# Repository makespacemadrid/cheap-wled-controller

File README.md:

Este proyecto nace de una práctica con Kicad en uno de los talleres de Makespace (slides de nuestro compañero Pablo Garrido [aquí](https://docs.google.com/presentation/d/1glYFRo9XCKRI-qDjp1DA8M3mJohLk-lrxx0JoBPsboM/edit?usp=drive_link)),
donde se diseñó el esquemático y el enrutado de la pcb para posterior fabricación de la misma en JLCPCB.

Continuando con el proceso lógico de aprendizaje, 
ahora este proyecto pretende servir como una primera aproximación en la práctica de soldadura SMD (componentes de montaje superficiales), 
así como fabricación de stencil usando una CNC (maquina de control numérico).

Junto al proyecto Kicad también se encuentran los stl de la carcasa para imprimirla en 3d.

El repositorio con el proyecto Kicad: https://github.com/makespacemadrid/cheap-wled-controller718714

Esta pcb tiene la particularidad de usar para su alimentación un usb c con PD (Power delivery), lo que permite negociar diferentes votlajes y de este modo usar tiras led que trabajen a 5v, 9v, 12v, etc.

## BOM 
### PCB
- [CH224K USB PD Protocol Sink Chip IC 10Pcs/lot](https://www.aliexpress.com/item/1005005284290184.html?spm=a2g0o.order_list.order_list_main.5.21ef194dDFnpwX)
- [AMS1117 3.3](https://www.aliexpress.com/item/1005005350284100.html?spm=a2g0o.order_list.order_list_main.544.21ef194dDFnpwX)
- ESP32-S3-WROOM-1-N4R
- [TPS54202DDC](https://lcsc.com/product-detail/DC-DC-Converters_TI-TPS54202DDCR_C191884.html?s_z=n_C191884)
- [MX5014S](https://lcsc.com/product-detail/Gate-Drivers_Wuxi-Maxinmicro-MX5014S_C5359091.html?s_z=n_C5359091)
- [ESDA25W](https://lcsc.com/product-detail/ESD-and-Surge-Protection-TVS-ESD_TECH-PUBLIC-ESDA25W_C3021136.html?s_z=n_C3021136)
- [receptor IR](https://lcsc.com/product-detail/Infrared-Receivers_VISHAY_TSOP38238_TSOP38238_C141632.html)
- diodo led footprint 0805
- [conector usb C](https://lcsc.com/product-detail/USB-Connectors_Korean-Hroparts-Elec-TYPE-C-31-M-12_C165948.html?s_z=n_C165948)
- [pin-header](https://lcsc.com/product-detail/Pin-Headers_Megastar-ZX-PZ2-0-2-5PZZ_C7501288.html?s_z=n_C7501288)
- [mosfet canal N](https://lcsc.com/product-detail/MOSFETs_YANGJIE-YJG100N04A_C919580.html?s_z=n_C919580)

### Stencil
- [fresa 3.175mmx15Dx0.1, CN](https://www.aliexpress.com/item/4000966103866.html?spm=a2g0o.order_list.order_list_main.509.21ef194dDFnpwX)
- una lata de refresco
- cinta de carrocero
- cinta de doble cara sin espuma. La que usamos nosotros es esta, comprada en papelerías Folder:
[comprada en papelerías Folder](/images/cinta_doble_cara.png)

### Carcasa
- 4 tornillos M3x6
- 4 insertos metálicos [Length 4mm, M3 (OD 5mm)](https://es.aliexpress.com/item/1005004870993068.html?spm=a2g0o.order_list.order_list_main.17.506f194dqZ3Ccw&gatewayAdapt=glo2esp)

## Tiras led
Las tiras led compatibles con el firmware son: https://kno.wled.ge/basics/compatible-led-strips/
- La tira led que usamos en el taller es esta: [WS2813 DC5V, White PCB, 2m 60 IP65](https://es.aliexpress.com/item/1005004289391906.html?spm=a2g0o.order_list.order_list_main.10.5d6c194dSriMHZ&gatewayAdapt=glo2esp)
- Para la alimentación sirve cualquier cargador de móvil con carga rápida, IKEA tiene [estos](https://www.ikea.com/es/es/p/sjoss-cargador-usb-1-puerto-30-w-carga-rapida-50549412/) a muy buen precio
- [conectores hembra y macho JST SM de 4 pines](https://es.aliexpress.com/item/1005004615616698.html)

## Fabricación de stencil
Usaremos el software Flatcam, en el que cargamos la capa "paste top" del gerber que generamos en Kicad para enviar a fabricar la PCB.
Esta capa contiene la geometría de los pads de todos los componentes. 

El proceso lo vamos a llevar a cabo con una fresa de 30 grados y 0.1 de diámetro. Asumiendo que la lata de refresco tiene un grosor de 0.2mm.
Las capturas de los pasos a seguir son las siguientes:

El gcode generado finalmente lo hemos subido [aquí](/includes/paste_top.gcode).

## Flasheo y configuración de firmware WLED

### Flasheo

En nuestro caso estamos usando un esp32 s3 con 4MB, por lo que vamos a flashear desde la web: https://wled-install.github.io/

### Configuración
En LED preferences:

La configuración de la tira:

La configuración del mosfet para apagar la tira:

El botón en placa permite encender y apagar la tira manualmente:

Para configurar el mando usaremos [este](/includes/18-key-ir.json) fichero json.

## Software necesario
- [Kicad](https://www.kicad.org/): Diseño pcb y generación de gerbers.
- [Flatcam](http://flatcam.org/): **Solo windows (adjuntamos el gcode ya generado)** Creación de gcode a partir del gerber para la fabricación del stencil
- [gSender](https://sienci.com/gsender/?srsltid=AfmBOopYPgWM8177GG6Q0knLP97hrF1G2skJw3ewIg3omObme7XnkDx5): Comunicación con la CNC para enviar el gcode
- [OrcaSlicer](https://orca-slicer.com/): Cualquier slicer para impresora 3d para fabricar la carcasa.

## Esquema de la placa

En este apartado se describen los componentes principales del circuito para gestionar la alimentación y regulación del voltaje de la tira LED.

---

### Información sobre el power delivery

📄 [UPD301A USB Power Delivery Operation](/datasheet/AN3265MicroChip.pdf)

📄 [A Primer on USB Type-C® and USB Power Delivery Applications and Requirements](/datasheet/PowerDeliveryTexas.pdf)

### 🔌 Conector USB-C

El conector USB-C que se utiliza en la placa tiene doce patillas con una separación muy pequeña entre cada una de ellas; además, en los dos extremos se encuentran los pines de alimentación (GND y VBUS), por lo que una mala soldadura podría generar un cortocircuito. 

> **Es importante que antes de conectar la placa se mida la resistencia entre los pines de alimentación para comprobar que no haya cortocircuito 🔥.**

---

### CH224K

El CH224K es el componente encargado de gestionar el protocolo *power delibery* (PD).

📄 [Descargar datasheet](https://github.com/makespacemadrid/cheap-wled-controller/blob/main/datasheet/ch224k.pdf)

- **Encapsulado:** ESSOP-10
- **Distribución de pines:**

| Pin No.     | Pin name | Pin type          | Pin description                                                                 |
|-------------|----------|-------------------|----------------------------------------------------------------------------------|
| 0           | GND      | Power             | Ground. Heat dissipation EPAD.                                                  |
| 1           | VDD      | Power             | Operating power input. Requires external 1uF decoupling capacitor. Connected in series with a resistor to VBUS. |
| 4, 5        | DP, DM   | Input/Output      | USB data line                                                                   |
| 6, 7        | CC1, CC2 | Input/Output      | Type-C CC data line                                                             |
| 2, 3, 9     | CFG1, CFG2, CFG3 | Analog input     | Power configuration input                                                       |
| 8           | VBUS     | Analog input      | Voltage detection input. Connected in series with a resistor to external VBUS.  |
| 10          | PG       | Open-drain output | Indicates Power Good by default. Active low. Can be customized.                |

- **Configuración de voltaje de salida:**

  Los pines encargados de  configurar la salida del voltaje son el 2, el 3 y el 9. En este caso solo se utiliza el pin 9, por lo que en función de la resistencia que se conecte a este pin, el voltaje de salida variará entre 5 y 20 voltios.

   >Por ejemplo, si se conecta una resistencia de 10 kΩ del pin 9 a tierra, el voltaje de salida (VBUS_CONN) será de 5 V.

  | Resistance on CFG to VDD | Request-voltage |
  |--------------------------|-----------------|
  | 10KΩ                     | 5V              |
  | 20KΩ                     | 9V              |
  | 47KΩ                     | 12V             |
  | 100KΩ                    | 15V             |
  | 200KΩ                    | 20V             |

---
### TPS54202

El voltaje que sale del CH224K entra en el *buck converter* TPS54202, que será el encargado de generar los 5 voltios estables del circuito.

📄 [Descargar datasheet](/datasheet/tps54202.pdf)

- **Encapsulado:** SOT-23
  
- **Distribución de pines:**

- **Configuración del circuito:**
  
  En el esquema del circuito se puede observar la configuración del componente, compuesta por resistencias, condensadores y la bobina L2, que mediante su carga (en forma de campo magnético) y descarga genera la corriente necesaria para alimentar los condensadores, que estabilizarán los 5 voltios de salida (+5V).

---
### AMS1117 3-3V

Una vez que se ha generado el voltaje +5V, el regulador de voltaje lineal (LDO) AMS1117 comienza a trabajar para entregar los 3,3V. Hay que tener en cuenta que la corriente máxima que puede entregar este regulador es de 1A. 

📄 [Descargar datasheet](/datasheet/ams1117.pdf)

- **Distribución de pines:**

  > PIN 1: GND
  >
  > PIN 2: VOUT
  >
  > PIN 3: VDD

- **Configuración del circuito:**

---
### ESP32-S3-WROOM-1-N4R2

📄 [Descargar datasheet](/datasheet/esp32-s3.pdf)

- **Distribución de pines:**

- **Configuración del circuito:**

---
### MX5014S

 La tira LED se alimenta a través del voltaje que se genera en el MOSFET Q3, que está controlado por el MX5014S, y que a su vez responde del IO47 del ESP32.

📄 [Descargar datasheet](/datasheet/mx5014s.pdf)

- **Distribución de pines:**

- **Configuración del circuito:**

## Líneas de voltaje principales

|Línea|Voltaje|Componente|
|-----|-------|----------|
|V_LED_|5-20V|CH224K|
|+5V|5V|TPS54202|
|+3.3V|3.3V|AMS1117|
|LED_1_VCC|5-20V|Q3

---
## Stencil con los valores de los componentes

---
## Autores
- [David Poza](http://github.com/davidpoza)
- [Jose David](http://github.com/jose8david)

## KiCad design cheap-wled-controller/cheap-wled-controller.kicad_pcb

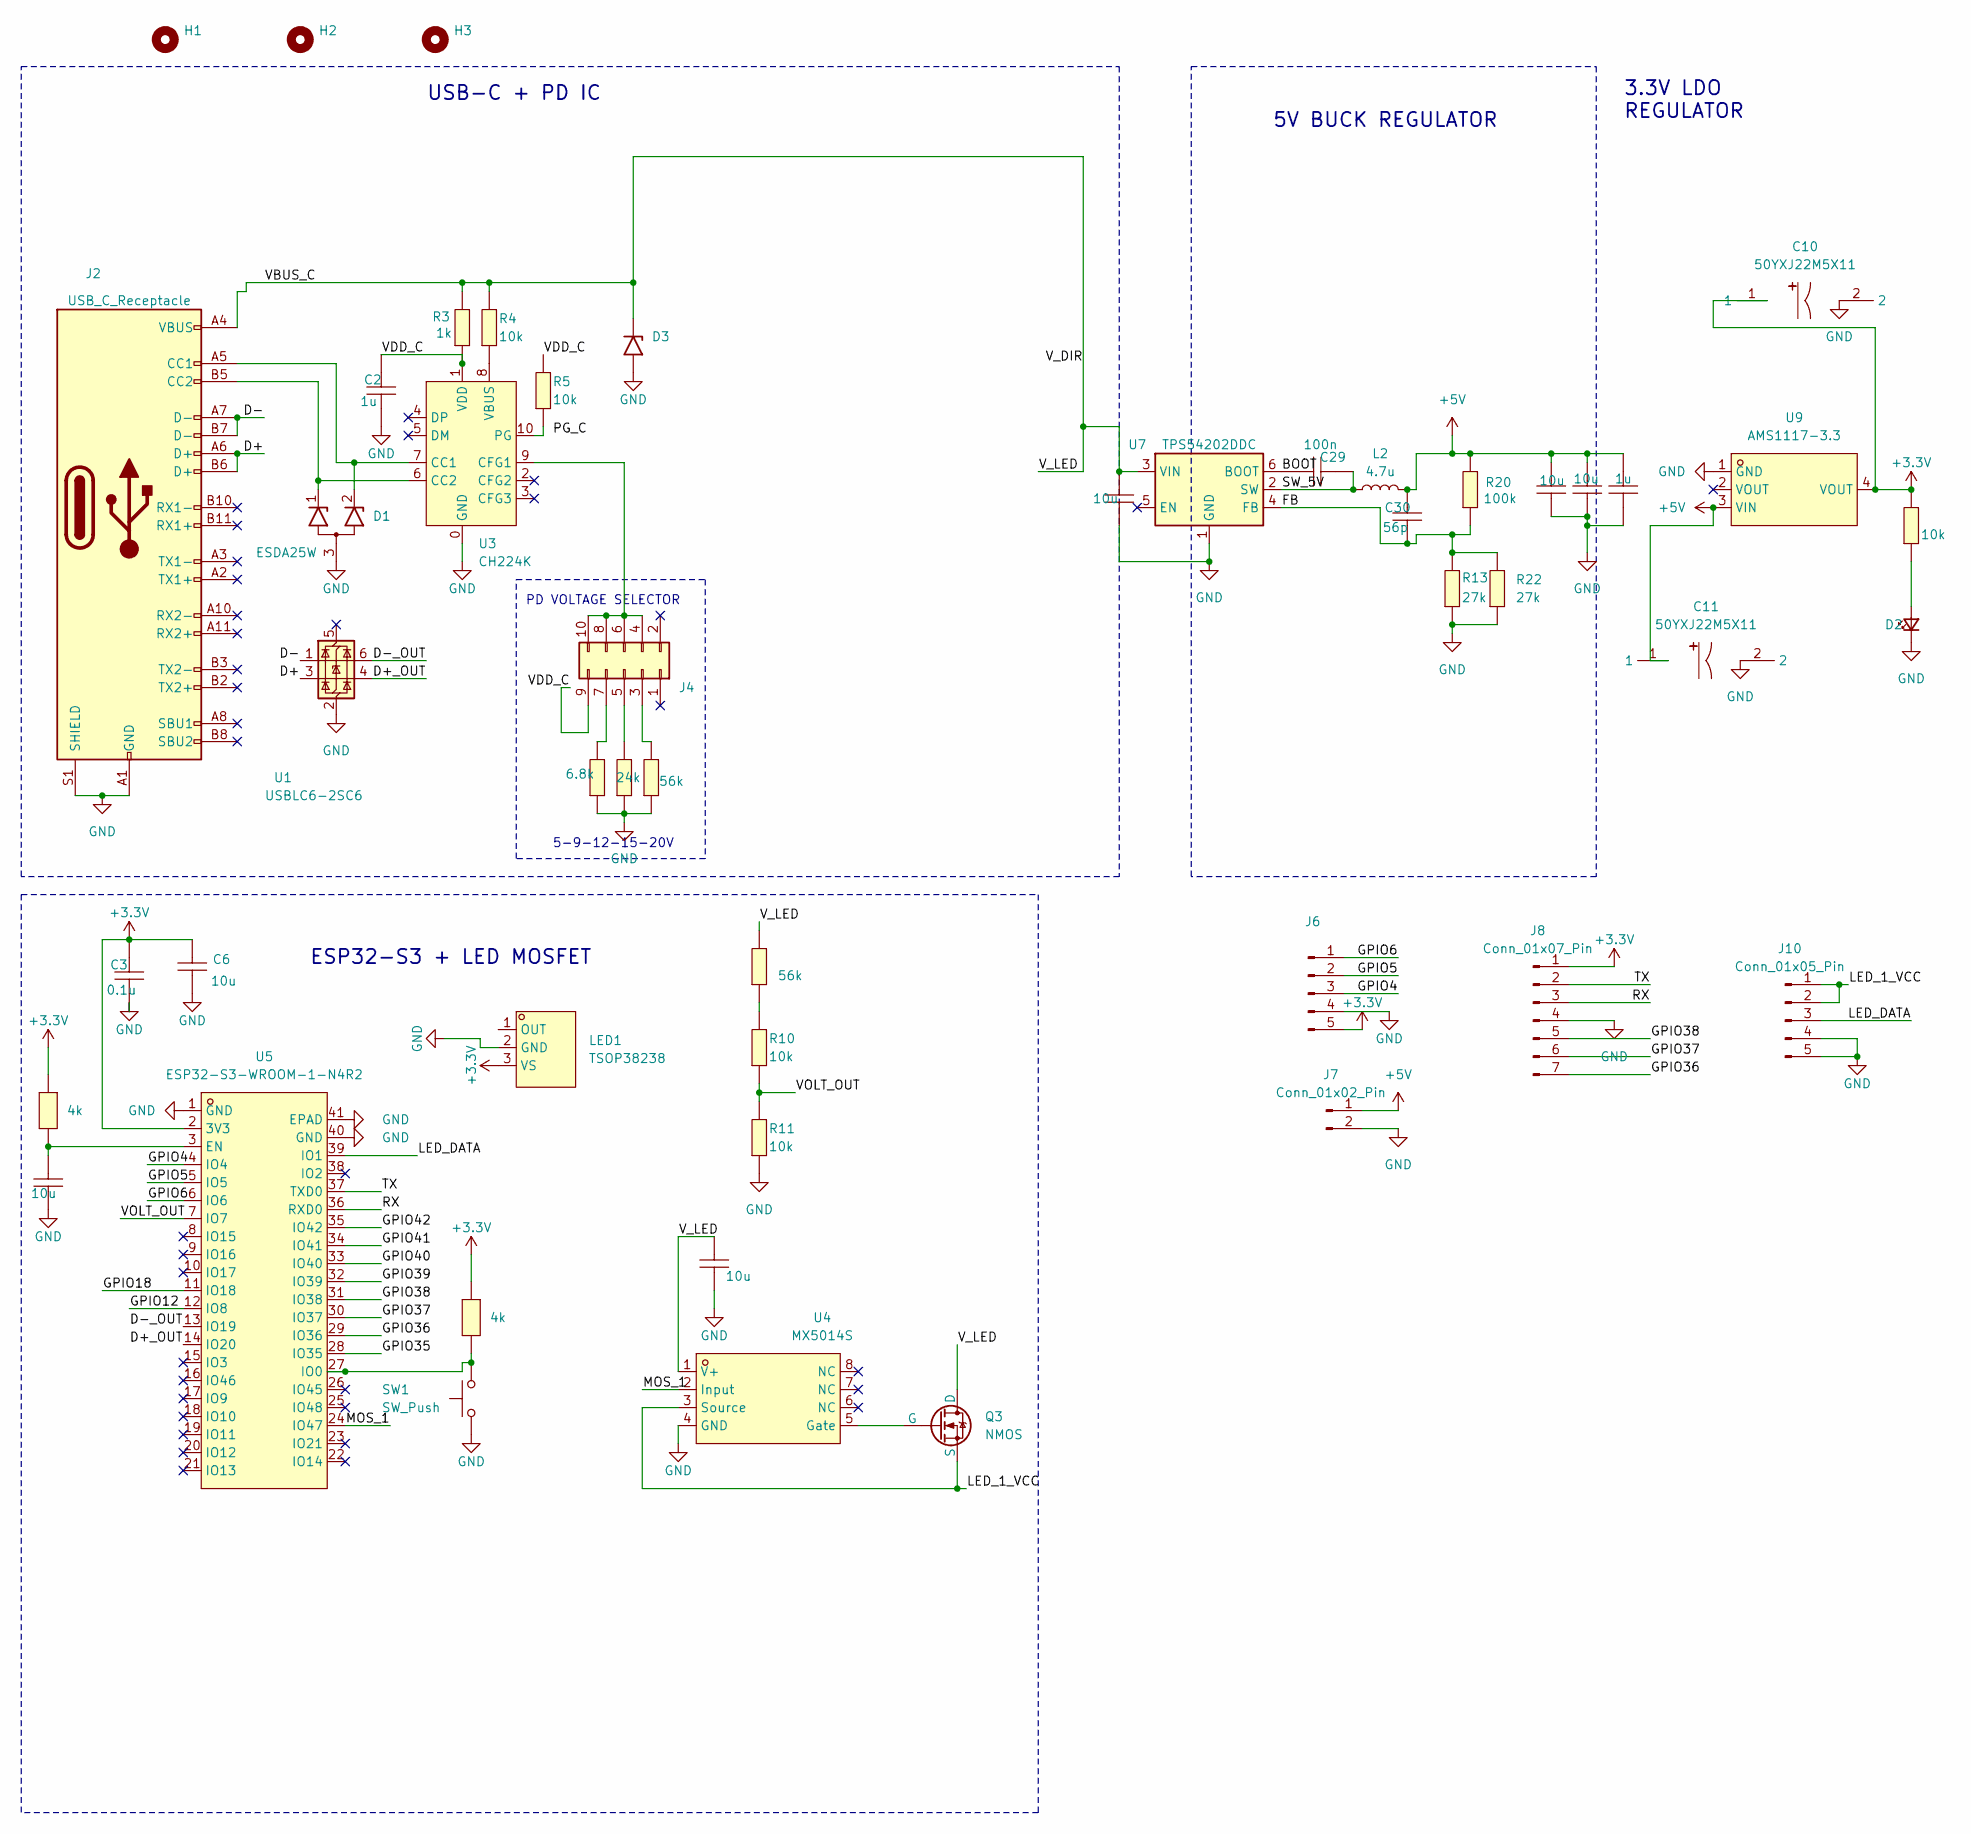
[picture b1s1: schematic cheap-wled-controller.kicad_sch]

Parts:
C1, C4, C5, C6, C7, C8: 10u; C0805; LCSC Part C1713
C2, C9: 1u; C0805; LCSC Part C215803
C3: 0.1u; C0805; LCSC Part C476766
C10, C11: 50YXJ22M5X11; CAP-TH_BD5.0-P2.00-D0.5-FD-1; LCSC Part C432364
C29: 100n; C0805; LCSC Part C476766
C30: 56p; C0805; LCSC Part C1828
D1: ESDA25W; SOT-323_SC-70; LCSC C3021136
D2: LED_Small; LED0805-R-RD; LCSC C5123548
D3: D_SMA; LCSC C383698
H1, H2, H3: MountingHole_3.2mm_M3
J2: USB_C_Receptacle; USB-C_SMD-TYPE-C-31-M-12; LCSC C165948
J4: Conn_02x05_Odd_Even; PinHeader_2x05_P2.00mm_Vertical; LCSC C7501288
J6: Conn_01x05_Pin; PinSocket_1x05_P2.54mm_Vertical
J7: Conn_01x02_Pin; JST_PH_B2B-PH-K_1x02_P2.00mm_Vertical; LCSC C131337
J8: Conn_01x07_Pin; PinSocket_1x07_P2.54mm_Vertical
J10: Conn_01x05_Pin; CONN-TH_5P-P3.81_KF124-3.81-5P; LCSC C72336
L2: 4.7u; L_1008_2520Metric; LCSC C91237
LED1: TSOP38238; SENSOR-TG_TSOP38236; LCSC Part C141632
Q3: NMOS; DFN-8_L5.9-W5.2-P1.27-LS6.2-BL; LCSC C919580
R2, R15: 56k; R0805; LCSC Part C17756
R3: 1k; R0805; LCSC Part C17513
R4, R5, R10, R11, R14: 10k; R0805; LCSC Part C17414
R6, R7: 4k; R0805; LCSC Part C2828855
R13, R22: 27k; R0805; LCSC Part C114533
R16: 24k; R0805; LCSC Part C17575
R17: 6.8k; R0805; LCSC Part C17772
R20: 100k; R0805; LCSC Part C149504
SW1: SW_Push; SW-SMD_TSA245G00D-250; LCSC C2846758
U1: USBLC6-2SC6; SOT-23-6; LCSC C2827654
U3: CH224K; ESSOP-10_L4.9-W3.9-P1.0-LS6.0-TL-EP; LCSC C970725
U4: MX5014S; SOIC-8_L4.9-W3.9-P1.27-LS6.0-BL; LCSC Part C5359091
U5: ESP32-S3-WROOM-1-N4R2; WIRELM-SMD_ESP32-S3-WROOM-1; LCSC Part C2913203
U7: TPS54202DDC; SOT-23-6; LCSC C191884
U9: AMS1117-3.3; SOT-223-3_L6.5-W3.4-P2.30-LS7.0-BR; LCSC Part C6186

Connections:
+3.3V: C3.2, C6.2, C10.1, J6.5, J8.1, LED1.3 (VS), R6.1, R7.1, R14.2, U5.2 (3V3), U9.4 (VOUT)
+5V: C4.2, C8.2, C9.2, C11.1, C30.2, J7.1, L2.2, R20.2, U9.3 (VIN)
/BOOT: C29.2, U7.6 (BOOT)
/D+: J2.A6 (D+), J2.B6 (D+), U1.3 (I/O2)
/D+_OUT: U1.4 (I/O2), U5.14 (IO20)
/D-: J2.A7 (D-), J2.B7 (D-), U1.1 (I/O1)
/D-_OUT: U1.6 (I/O1), U5.13 (IO19)
/FB: C30.1, R13.2, R20.1, R22.2, U7.4 (FB)
/GPIO4: J6.3, U5.4 (IO4)
/GPIO5: J6.2, U5.5 (IO5)
/GPIO6: J6.1, U5.6 (IO6)
/GPIO12: U5.12 (IO8)
/GPIO18: U5.11 (IO18)
/GPIO35: U5.28 (IO35)
/GPIO36: J8.7, U5.29 (IO36)
/GPIO37: J8.6, U5.30 (IO37)
/GPIO38: J8.5, U5.31 (IO38)
/GPIO39: U5.32 (IO39)
/GPIO40: U5.33 (IO40)
/GPIO41: LED1.1 (OUT), U5.34 (IO41)
/GPIO42: U5.35 (IO42)
/LED_1_VCC: J10.1, J10.2, Q3.3 (S), U4.3 (Source)
/LED_DATA: J10.3, U5.39 (IO1)
/MOS_1: U4.2 (Input), U5.24 (IO47)
/RX: J8.3, U5.36 (RXD0)
/SW_5V: C29.1, L2.1, U7.2 (SW)
/TX: J8.2, U5.37 (TXD0)
/VBUS_C: C1.2, C5.2, D3.1 (A1), J2.A4 (VBUS), J2.A9 (VBUS), J2.B4 (VBUS), J2.B9 (VBUS), Q3.2 (D), R3.2, R4.2, R15.2, U4.1 (V+), U7.3 (VIN)
/VDD_C: C2.2, J4.9, R3.1, R5.2, U3.1 (VDD)
/VOLT_OUT: R10.1, R11.2, U5.7 (IO7)
GND: C1.1, C2.1, C3.1, C4.1, C5.1, C6.1, C7.1, C8.1, C9.1, C10.2, C11.2, D1.3 (A), D2.1 (K), D3.2 (A2), J2.0, J2.1, J2.2, J2.3, J2.A1 (GND), J2.A12 (GND), J2.B1 (GND), J2.B12 (GND), J2.S1 (SHIELD), J6.4, J7.2, J8.4, J10.4, J10.5, LED1.2 (GND), R2.1, R11.1, R13.1, R16.1, R17.1, R22.1, SW1.1, U1.2 (GND), U3.0 (GND), U3.11, U4.4 (GND), U5.1 (GND), U5.40 (GND), U5.41 (EPAD), U7.1 (GND), U9.1 (GND)
unnamed: D1.1 (K1), J2.B5 (CC2), U3.6 (CC2)
unnamed: D1.2 (K2), J2.A5 (CC1), U3.7 (CC1)
unnamed: D2.2 (A), R14.1
unnamed: J4.3, R2.2
unnamed: J4.5, R16.2
unnamed: J4.7, R17.2
unnamed: J4.4, J4.6, J4.8, J4.10, U3.9 (CFG1)
unnamed: Q3.1 (G), U4.5 (Gate)
unnamed: R10.2, R15.1
unnamed: R5.1, U3.10 (PG)
unnamed: R4.1, U3.8 (VBUS)
unnamed: C7.2, R6.2, U5.3 (EN)
unnamed: R7.2, SW1.2, U5.27 (IO0)

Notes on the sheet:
ESP32-S3 + LED MOSFET
USB-C + PD IC
5V BUCK REGULATOR
5-9-12-15-20V
PD VOLTAGE SELECTOR
3.3V LDO REGULATOR

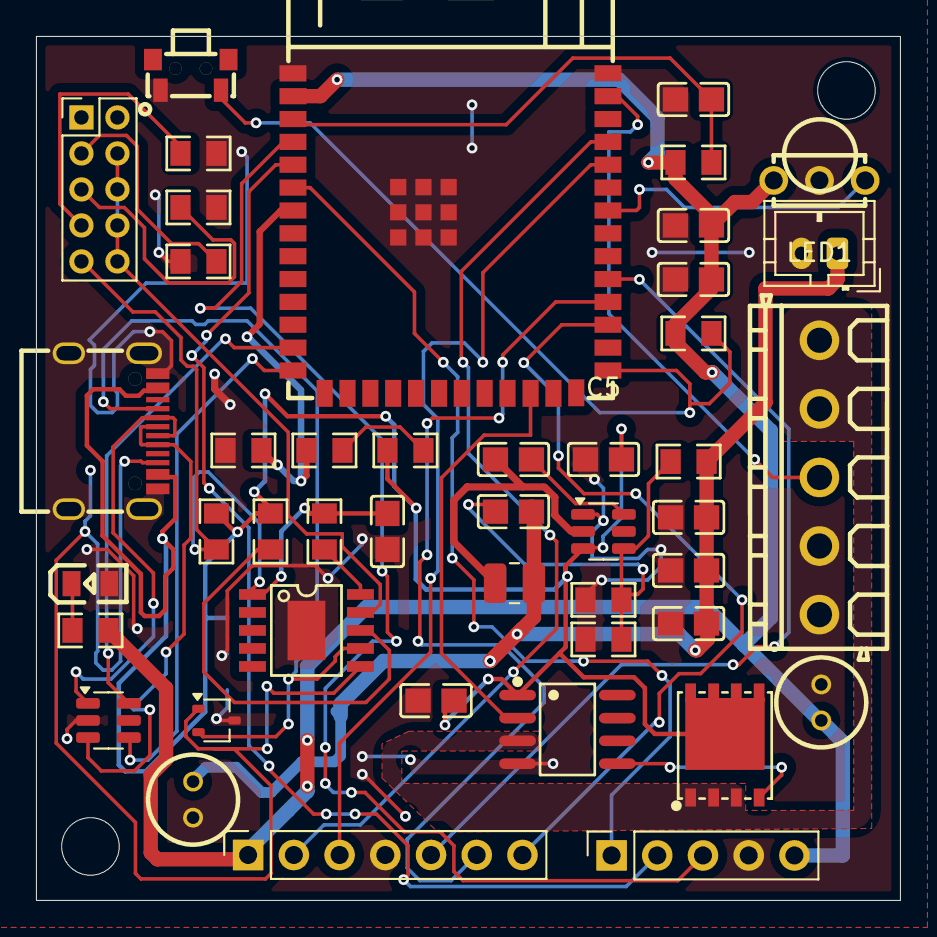
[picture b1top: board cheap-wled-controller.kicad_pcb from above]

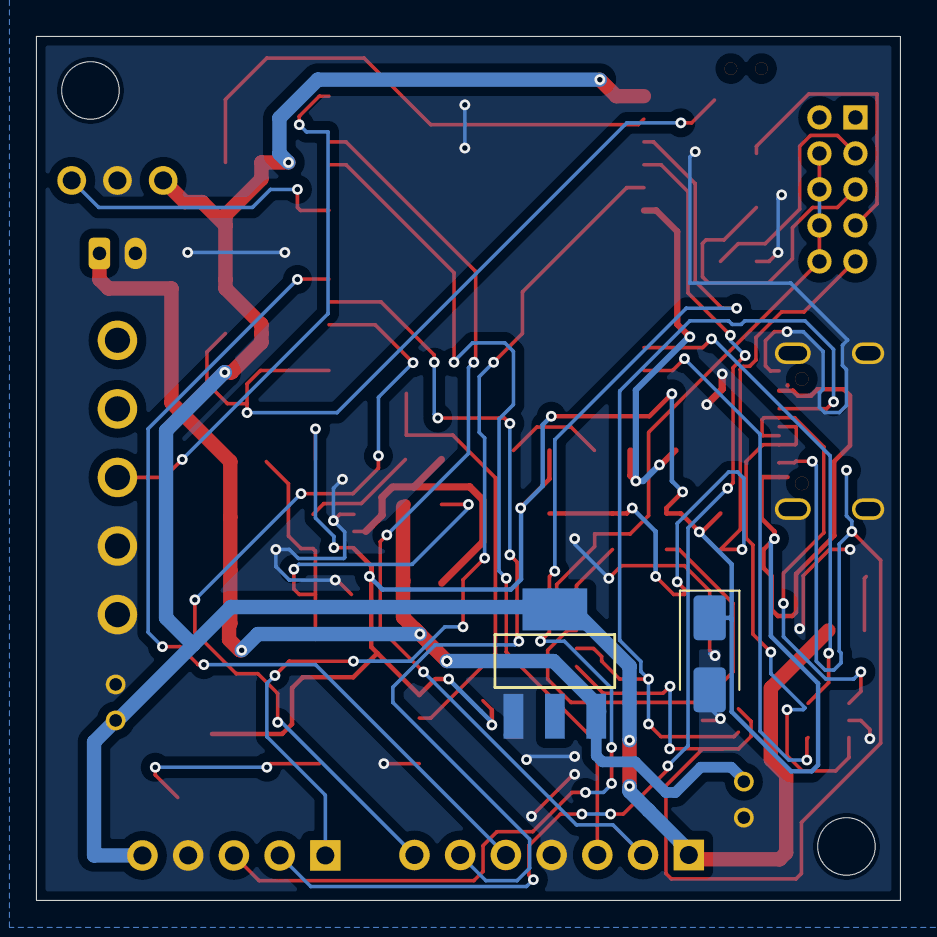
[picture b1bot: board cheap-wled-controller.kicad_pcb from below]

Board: 2 copper layers, 48.0 x 48.0 mm, 49 parts (2 on the bottom side), 38 nets.

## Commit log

2025-01-26 voltage selector
2025-01-26 footprint problem solved
2025-01-29 etapa de 5v a 3v
2025-01-30 fusible
2025-02-02 refactor using 0805 components
2025-02-02 esp32 s3
2025-02-04 all footprints added
2025-02-04 leds added
2025-02-06 some traces
2025-02-08 pcb fixes
2025-02-15 drc fixes
2025-02-16 added gerber
2025-02-19 added panelized gerber
2025-02-19 added some GND for the esp32
2025-02-19 right position for the holes
2025-03-19 new design mini 5x5
2025-03-22 all tracks connected
2025-03-23 added capacitors for ams1117 and TSOP38238
2025-03-23 gerbers
2025-03-25 fixes
2025-07-20 added case stl
2025-07-24 Información sobre el componente ch224k
2025-07-24 final result image
2025-07-24 Descripción del componente ch224k
2025-07-24 added BOM
2025-07-24 Componentes del circuito: CH224K y buck converted
2025-07-25 Componentes principales del circuito
2025-07-25 Esquema de la placa completo
2025-07-25 Cambio color fondo capturas
2025-07-25 Líneas de voltaje
2025-07-25 added more items in BOM
2025-07-25 removed embedded image
2025-07-25 added IR config
2025-07-25 link to firmware
2025-07-25 Texto final
2025-07-25 flatcam process
2025-07-25 flashing process
2025-07-25 Actualizo con la información del esquemático
2025-07-25 Stencil con valores
2025-07-28 Añado información sobre el power delivery
